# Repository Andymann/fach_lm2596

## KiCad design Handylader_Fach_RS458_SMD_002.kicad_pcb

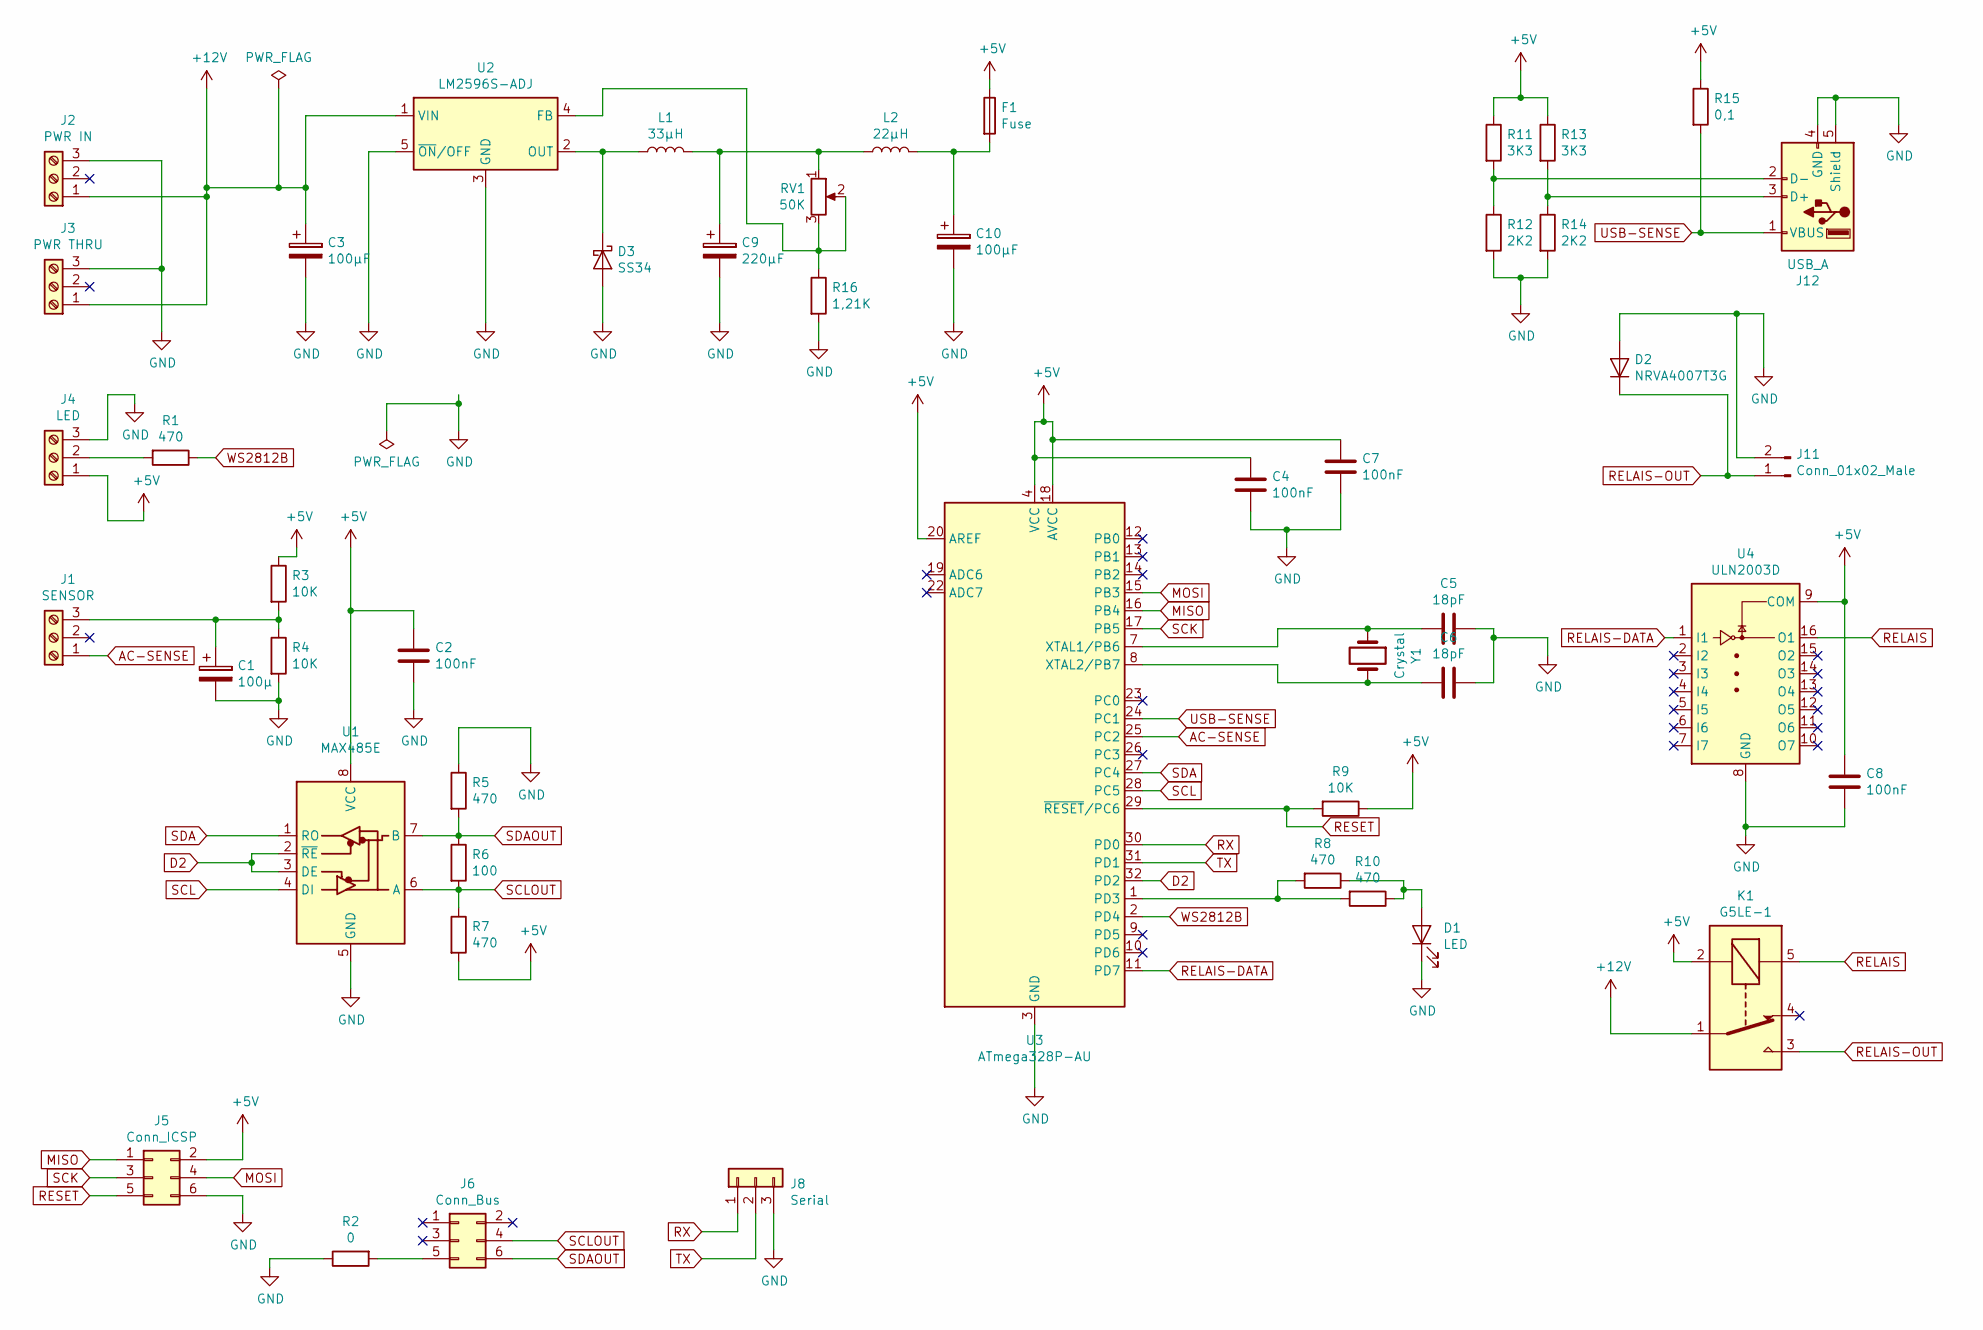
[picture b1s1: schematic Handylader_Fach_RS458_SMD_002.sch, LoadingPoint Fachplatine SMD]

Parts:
C1: 100µ; C_0603_1608Metric
C2, C4, C7, C8: 100nF; C_0603_1608Metric
C3, C10: 100µF; CP_Elec_8x10
C5, C6: 18pF; C_0603_1608Metric
C9: 220µF; CP_Elec_8x10
D1: LED; LED_0603_1608Metric
D2: NRVA4007T3G; D_SMA
D3: SS34; D_SMC
F1: Fuse; SolderJumper-2_P1.3mm_Open_Pad1.0x1.5mm
J1: SENSOR; TerminalBlock_TE_282834-3_1x03_P2.54mm_Horizontal
J2: PWR IN; TerminalBlock_TE_282834-3_1x03_P2.54mm_Horizontal
J3: PWR THRU; TerminalBlock_TE_282834-3_1x03_P2.54mm_Horizontal
J4: LED; TerminalBlock_TE_282834-3_1x03_P2.54mm_Horizontal
J5: Conn_ICSP; PinHeader_2x03_P2.54mm_Vertical_SMD
J6: Conn_Bus; PinHeader_2x03_P2.54mm_Vertical_SMD
J8: Serial; PinHeader_1x03_P2.54mm_Vertical
J11: Conn_01x02_Male; PinHeader_1x02_P2.54mm_Vertical
J12: USB_A; Wurth_USB_A_62900416021
K1: G5LE-1; Relay_SPDT_Omron-G5LE-1
L1: 33µH; L_12x12mm_H8mm
L2: 22µH; L_6.3x6.3_H3
R1, R5, R7, R8, R10: 470; R_0603_1608Metric
R2: 0; R_0603_1608Metric
R3, R4, R9: 10K; R_0603_1608Metric
R6: 100; R_0603_1608Metric
R11, R13: 3K3; R_0603_1608Metric
R12, R14: 2K2; R_0603_1608Metric
R15: 0,1; R_0603_1608Metric
R16: 1,21K; R_0603_1608Metric
RV1: 50K; Potentiometer_ACP_CA6-VSMD_Vertical
U1: MAX485E; SOIC-8_3.9x4.9mm_P1.27mm
U2: LM2596S-ADJ; TO-263-5_TabPin3
U3: ATmega328P-AU; TQFP-32_7x7mm_P0.8mm
U4: ULN2003D; SOIC-16_3.9x9.9mm_P1.27mm
Y1: Crystal; Crystal_SMD_HC49-SD

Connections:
+5V: C2.1, C4.1, C7.1, C8.1, F1.1, J4.1, J5.2, K1.2, R3.1, R7.2, R9.1, R11.1, R13.1, R15.1, U1.8 (VCC), U3.4 (VCC), U3.6 (VCC), U3.18 (AVCC), U3.20 (AREF), U4.9 (COM)
+12V: C3.1, J2.1, J3.1, K1.1, U2.1 (VIN)
AC-SENSE: J1.1, U3.25 (PC2)
D2: U1.2 (~RE), U1.3 (DE), U3.32 (PD2)
GND: C1.2, C2.2, C3.2, C4.2, C5.1, C6.1, C7.2, C8.2, C9.2, C10.2, D1.1 (K), D2.2 (A), D3.2 (A), J2.3, J3.3, J4.3, J5.6, J8.3, J11.2, J12.4 (GND), J12.5 (Shield), R2.1, R4.2, R5.1, R12.2, R14.2, R16.2, U1.5 (GND), U2.3 (GND), U2.5 (~ON~/OFF), U3.3 (GND), U3.5 (GND), U3.21 (GND), U4.8 (GND)
MISO: J5.1, U3.16 (PB4)
MOSI: J5.4, U3.15 (PB3)
unnamed: C1.1, J1.3, R3.2, R4.1
unnamed: C5.2, U3.7 (XTAL1/PB6), Y1.1
unnamed: C6.2, U3.8 (XTAL2/PB7), Y1.2
unnamed: C9.1, L1.2, L2.1, RV1.1
unnamed: C10.1, F1.2, L2.2
unnamed: D1.2 (A), R8.1, R10.1
unnamed: D3.1 (K), L1.1, U2.2 (OUT)
unnamed: J4.2, R1.2
unnamed: J6.5, R2.2
unnamed: J12.2 (D-), R11.2, R12.1
unnamed: J12.3 (D+), R13.2, R14.1
unnamed: R8.2, R10.2, U3.1 (PD3)
unnamed: R16.1, RV1.2, RV1.3, U2.4 (FB)
RELAIS: K1.5, U4.16 (O1)
RELAIS-DATA: U3.11 (PD7), U4.1 (I1)
RELAIS-OUT: D2.1 (K), J11.1, K1.3
RESET: J5.5, R9.2, U3.29 (~RESET~/PC6)
RX: J8.1, U3.30 (PD0)
SCK: J5.3, U3.17 (PB5)
SCL: U1.4 (DI), U3.28 (PC5)
SCLOUT: J6.4, R6.2, R7.1, U1.6 (A)
SDA: U1.1 (RO), U3.27 (PC4)
SDAOUT: J6.6, R5.2, R6.1, U1.7 (B)
TX: J8.2, U3.31 (PD1)
USB-SENSE: J12.1 (VBUS), R15.2, U3.24 (PC1)
WS2812B: R1.1, U3.2 (PD4)

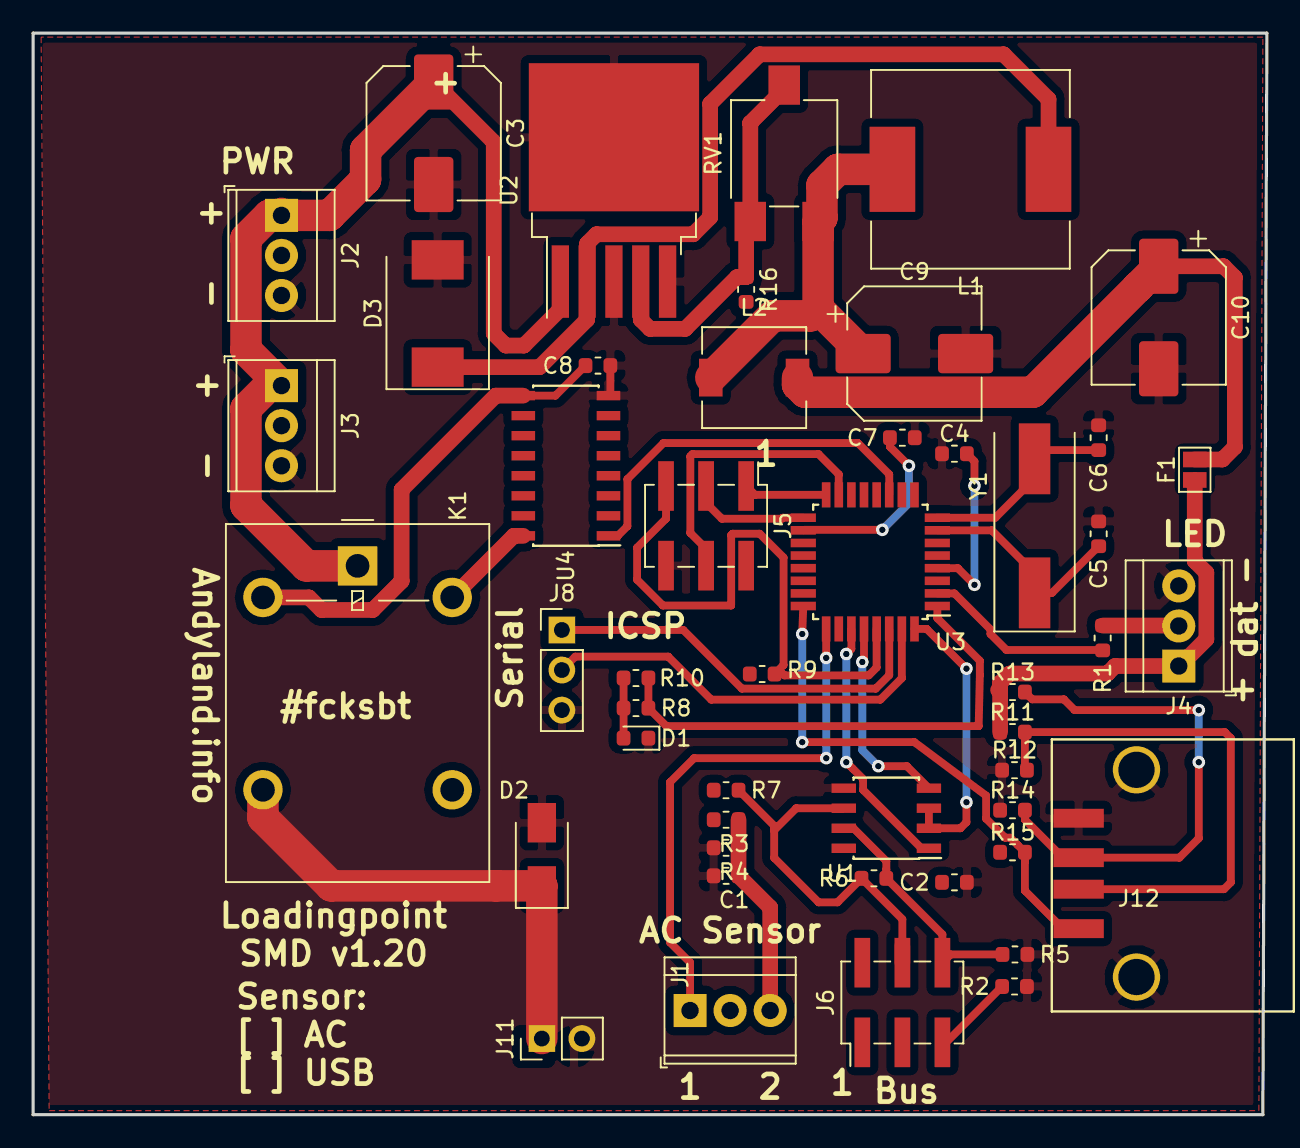
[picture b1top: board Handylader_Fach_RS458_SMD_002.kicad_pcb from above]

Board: 2 copper layers, 78.2 x 68.6 mm, 48 parts (0 on the bottom side), 33 nets.
